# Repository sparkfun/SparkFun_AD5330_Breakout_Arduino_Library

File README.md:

AD5330 Breakout Arduino Library
===============

[ 
*Breakout Board for AD5330 Parallel 8-Bit DAC (BOB-12082)*](https://www.sparkfun.com/products/12082)

This is a breakout board for Analog Device's AD5330 8-bit digital-to-analog converter. 
It runs from 2.5 to 5.5V. 

Repository Contents
-------------------

* **/examples** - Example sketches for the library (.ino). Run these from the Arduino IDE. 
* **/extras** - Additional documentation for the user. These files are ignored by the IDE. 
* **/src** - Source files for the library (.cpp, .h).
* **keywords.txt** - Keywords from this library that will be highlighted in the Arduino IDE. 
* **library.properties** - General library properties for the Arduino package manager. 

Documentation
--------------

* **[Installing an Arduino Library Guide](https://learn.sparkfun.com/tutorials/installing-an-arduino-library)** - Basic information on how to install an Arduino library.
* **[Product Repository](https://github.com/sparkfun/AD5330_Breakout)** - Main repository (including hardware files) for the AD5330 Breakout.
* **[Tutorial](http://www.sparkfun.com/commerce/tutorial_info.php?tutorials_id=160)** - Basic tutorial for the AD5330 Breakout.

Version History
---------------

* [V_1.2.2](https://github.com/sparkfun/AD5330_Breakout_Arduino_Library/tree/V_1.2.2) - Edited README.txt
* [V_1.2.1](https://github.com/sparkfun/AD5330_Breakout_Arduino_Library/tree/V_1.2.1) - Fixed library.properties file
* [V1.2](https://github.com/sparkfun/AD5330_Breakout_Arduino_Library/tree/V_1.2) - Arduino library format
* [V1.1](https://www.sparkfun.com/products/9719) 

License Information
-------------------
The hardware is released under [Creative Commons Share-alike 3.0](http://creativecommons.org/licenses/by-sa/3.0/).  
All other code is open source so please feel free to do anything you want with it; you buy me a beer if you use this and we meet someday ([Beerware license](http://en.wikipedia.org/wiki/Beerware)).

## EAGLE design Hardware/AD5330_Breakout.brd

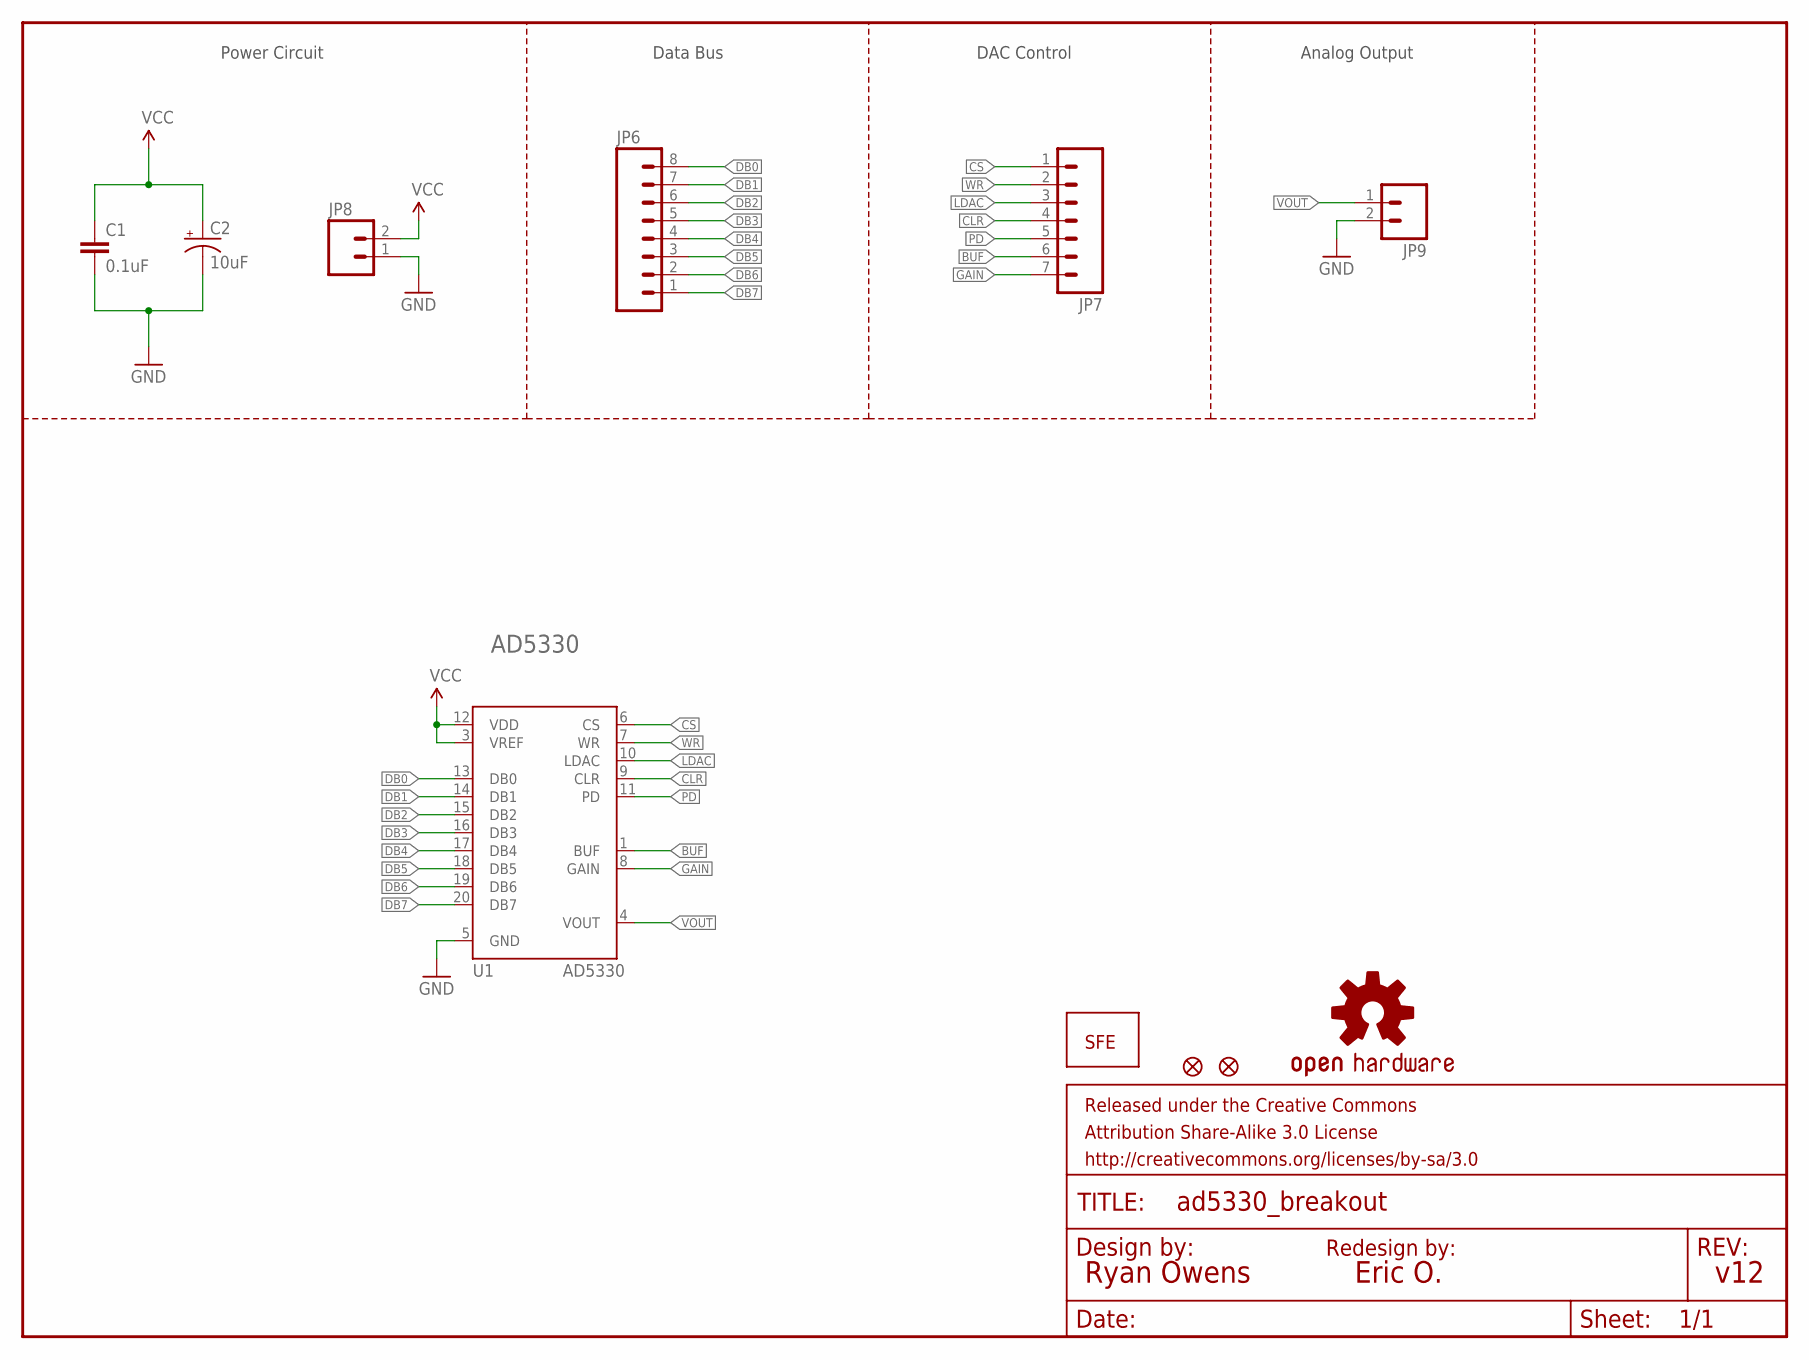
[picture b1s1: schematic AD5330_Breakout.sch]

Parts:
C1: 0.1uF; 0603-CAP
C2: 10uF; EIA3216
FRAME1: FRAME-LETTER; CREATIVE_COMMONS
JP1: LOGO-SFENEW; SFE-NEW-WEBLOGO
JP2, JP3: FIDUCIAL1X2; FIDUCIAL-1X2
JP6: M08; 1X08
JP7: M07; 1X07
JP8, JP9: M02PTH; 1X02
LOGO1: OSHW-LOGOS; OSHW-LOGO-S
U1: AD5330; TSSOP20

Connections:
BUF: JP7.6, U1.1 (BUF)
CLR: JP7.4, U1.9 (CLR)
CS: JP7.1, U1.6 (CS)
DB0: JP6.8, U1.13 (DB0)
DB1: JP6.7, U1.14 (DB1)
DB2: JP6.6, U1.15 (DB2)
DB3: JP6.5, U1.16 (DB3)
DB4: JP6.4, U1.17 (DB4)
DB5: JP6.3, U1.18 (DB5)
DB6: JP6.2, U1.19 (DB6)
DB7: JP6.1, U1.20 (DB7)
GAIN: JP7.7, U1.8 (GAIN)
GND: C1.2, C2.C (-), JP8.1, JP9.2, U1.5 (GND)
LDAC: JP7.3, U1.10 (LDAC)
PD: JP7.5, U1.11 (PD)
VCC: C1.1, C2.A (+), JP8.2, U1.3 (VREF), U1.12 (VDD)
VOUT: JP9.1, U1.4 (VOUT)
WR: JP7.2, U1.7 (WR)

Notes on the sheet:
Power Circuit
Data Bus
DAC Control
Analog Output
v12
Ryan Owens
Redesign by:
Eric O.
AD5330

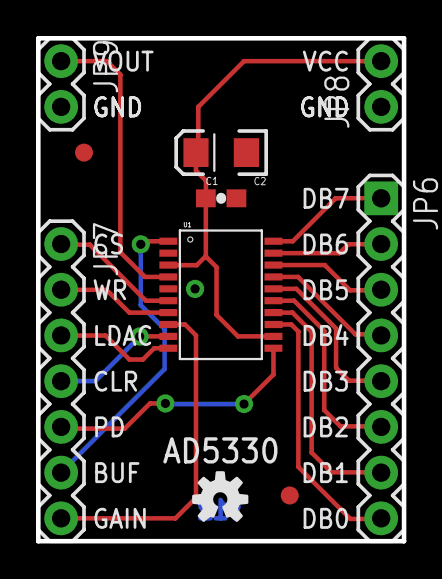
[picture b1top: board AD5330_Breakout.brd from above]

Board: 2 copper layers, 20.3 x 27.9 mm, 12 parts (1 on the bottom side), 18 nets.

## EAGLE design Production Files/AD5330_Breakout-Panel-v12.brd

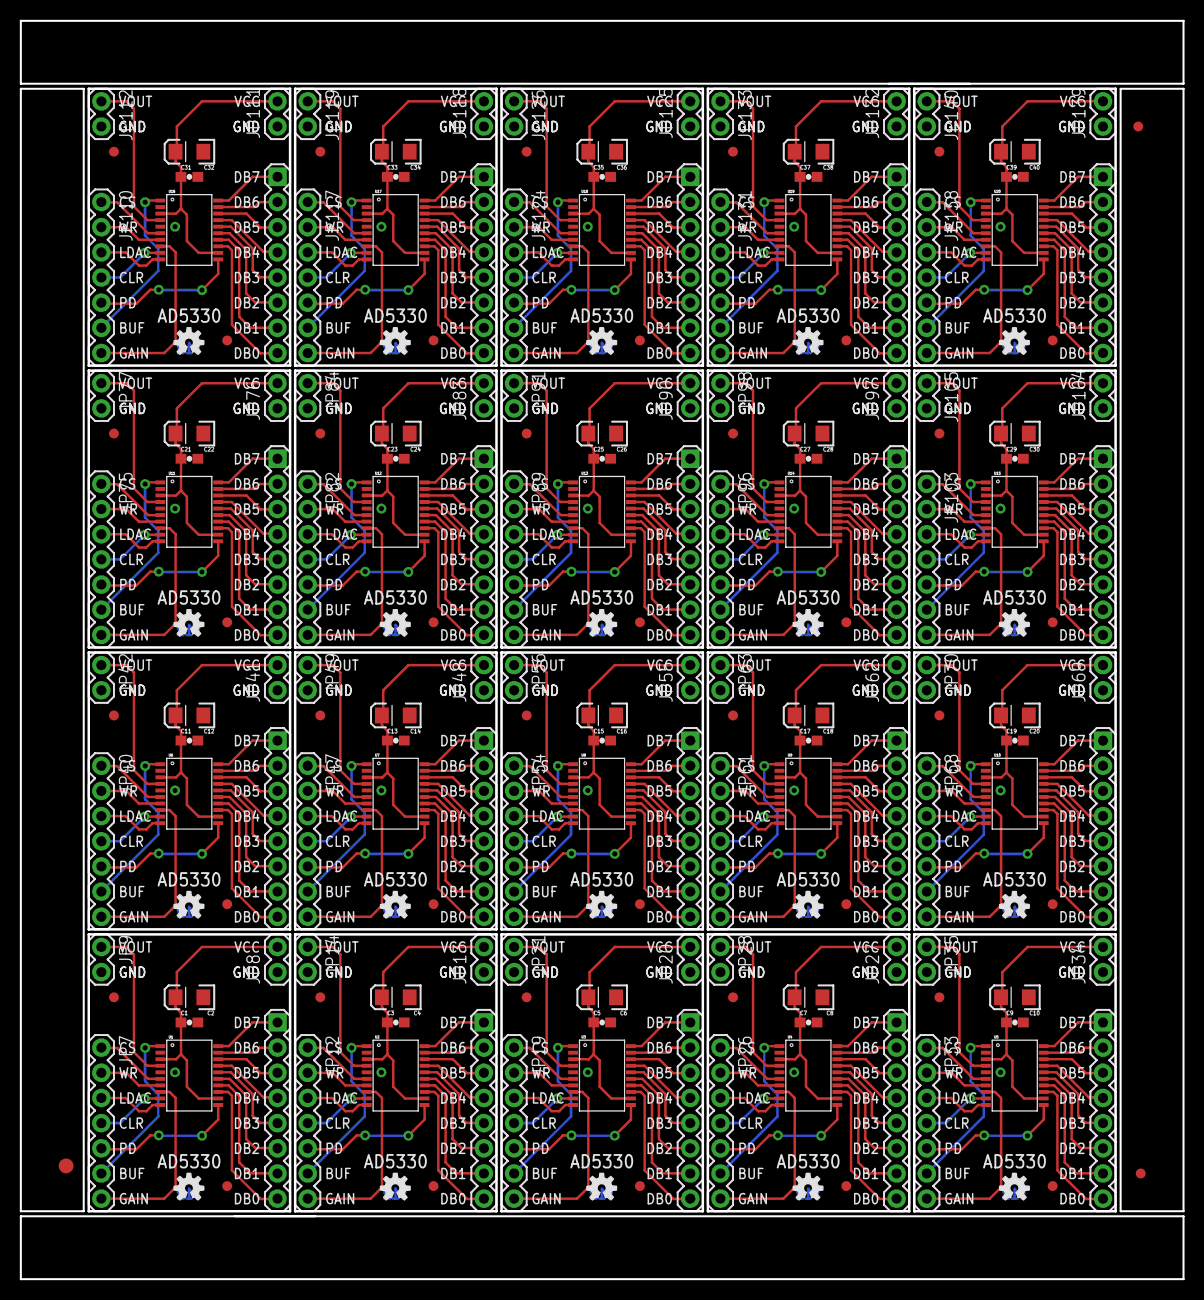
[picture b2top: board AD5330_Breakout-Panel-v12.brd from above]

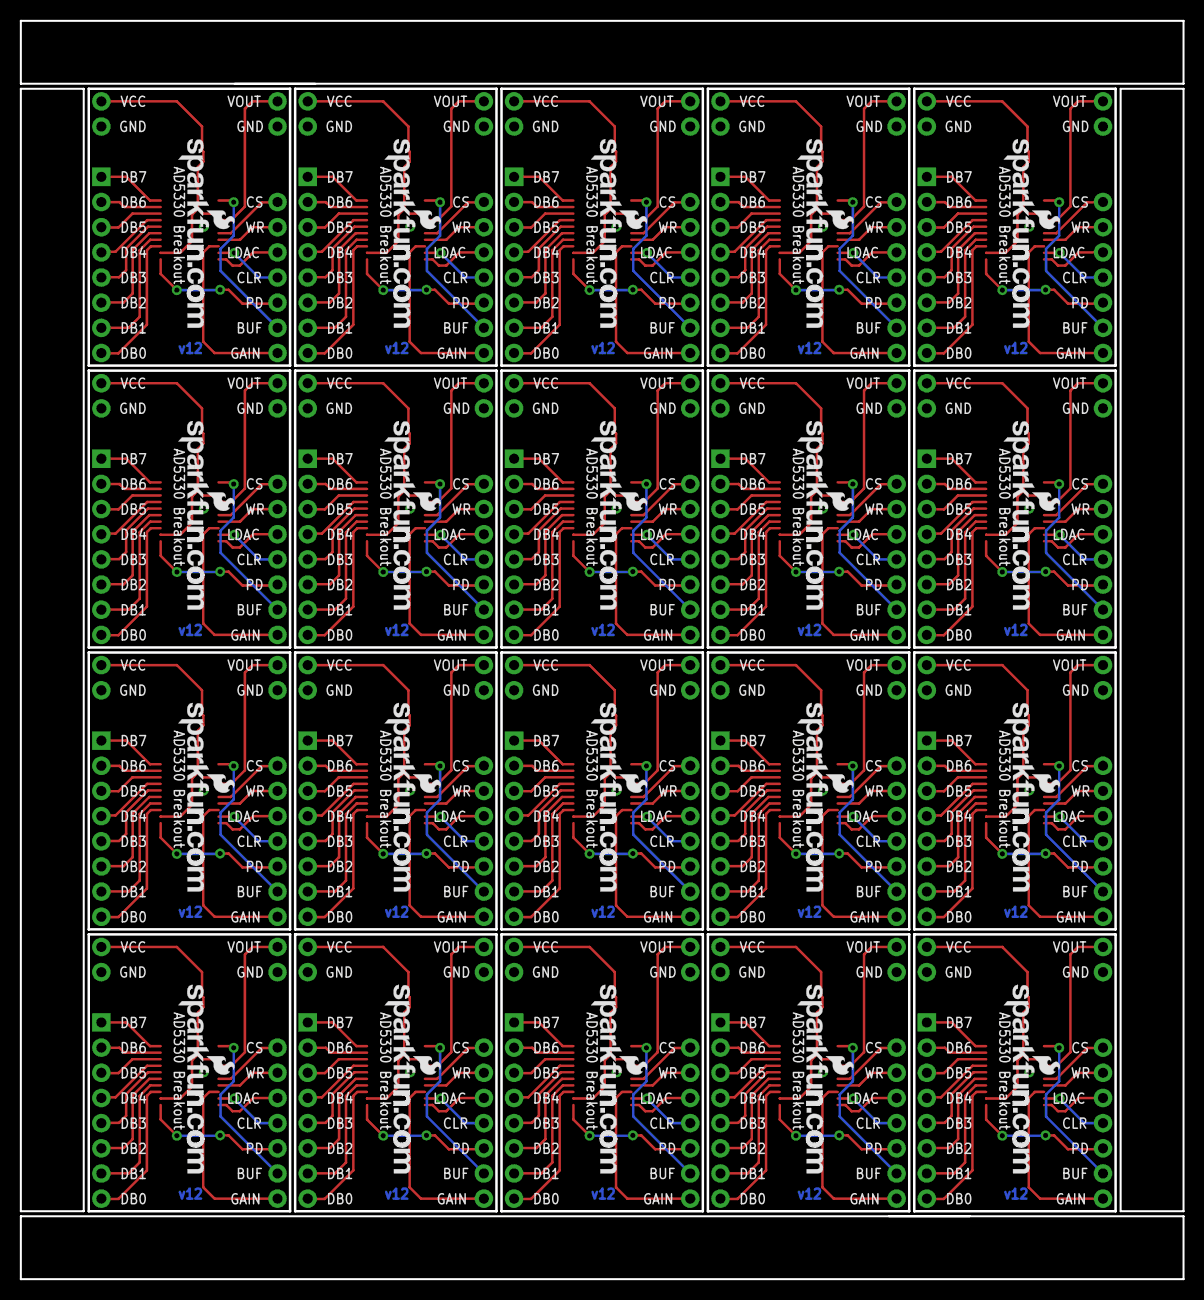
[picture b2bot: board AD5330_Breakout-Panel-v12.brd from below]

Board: 2 copper layers, 117.3 x 126.9 mm, 223 parts (20 on the bottom side), 360 nets.

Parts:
C1, C3, C5, C7, C9, C11, C13, C15, C17, C19, C21, C23, C25, C27, C29, C31, C33, C35, C37, C39: 0.1uF; 0603-CAP
C2, C4, C6, C8, C10, C12, C14, C16, C18, C20, C22, C24, C26, C28, C30, C32, C34, C36, C38, C40: 10uF; EIA3216
E$1: FIDUCIAL-1.5X3
E$4, E$5: FIDUCIAL-1X2
JP1, JP4, JP15, JP22, JP29, JP36, JP43, JP50, JP57, JP64, JP71, JP78, JP85, JP92, JP99, JP106, JP113, JP120, JP127, JP134: LOGO-SFENEW; SFE-NEW-WEBLOGO
JP2, JP3, JP5, JP10, JP16, JP17, JP23, JP24, JP30, JP31, JP37, JP38, JP44, JP45, JP51, JP52, JP58, JP59, JP65, JP66, JP72, JP73, JP79, JP80, JP86, JP87, JP93, JP94, JP100, JP101, JP107, JP108, JP114, JP115, JP121, JP122, JP128, JP129, JP135, JP136: FIDUCIAL1X2; FIDUCIAL-1X2
JP6, JP11, JP18, JP25, JP32, JP39, JP46, JP53, JP60, JP67, JP74, JP81, JP88, JP95, JP102, JP109, JP116, JP123, JP130, JP137: 1X08
JP7, JP12, JP19, JP26, JP33, JP40, JP47, JP54, JP61, JP68, JP75, JP82, JP89, JP96, JP103, JP110, JP117, JP124, JP131, JP138: 1X07
JP8, JP9, JP13, JP14, JP20, JP21, JP27, JP28, JP34, JP35, JP41, JP42, JP48, JP49, JP55, JP56, JP62, JP63, JP69, JP70, JP76, JP77, JP83, JP84, JP90, JP91, JP97, JP98, JP104, JP105, JP111, JP112, JP118, JP119, JP125, JP126, JP132, JP133, JP139, JP140: 1X02
LOGO1, LOGO2, LOGO3, LOGO4, LOGO5, LOGO6, LOGO7, LOGO8, LOGO9, LOGO10, LOGO11, LOGO12, LOGO13, LOGO14, LOGO15, LOGO16, LOGO17, LOGO18, LOGO19, LOGO20: OSHW-LOGOS; OSHW-LOGO-S
U1, U2, U3, U4, U5, U6, U7, U8, U9, U10, U11, U12, U13, U14, U15, U16, U17, U18, U19, U20: AD5330; TSSOP20

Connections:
BUF: JP7.6, U1.1
BUF1: JP12.6, U2.1
BUF2: JP19.6, U3.1
BUF3: JP26.6, U4.1
BUF4: JP33.6, U5.1
BUF5: JP40.6, U6.1
BUF6: JP47.6, U7.1
BUF7: JP54.6, U8.1
BUF8: JP61.6, U9.1
BUF9: JP68.6, U10.1
BUF10: JP75.6, U11.1
BUF11: JP82.6, U12.1
BUF12: JP89.6, U13.1
BUF13: JP96.6, U14.1
BUF14: JP103.6, U15.1
BUF15: JP110.6, U16.1
BUF16: JP117.6, U17.1
BUF17: JP124.6, U18.1
BUF18: JP131.6, U19.1
BUF19: JP138.6, U20.1
CLR: JP7.4, U1.9
CLR1: JP12.4, U2.9
CLR2: JP19.4, U3.9
CLR3: JP26.4, U4.9
CLR4: JP33.4, U5.9
CLR5: JP40.4, U6.9
CLR6: JP47.4, U7.9
CLR7: JP54.4, U8.9
CLR8: JP61.4, U9.9
CLR9: JP68.4, U10.9
CLR10: JP75.4, U11.9
CLR11: JP82.4, U12.9
CLR12: JP89.4, U13.9
CLR13: JP96.4, U14.9
CLR14: JP103.4, U15.9
CLR15: JP110.4, U16.9
CLR16: JP117.4, U17.9
CLR17: JP124.4, U18.9
CLR18: JP131.4, U19.9
CLR19: JP138.4, U20.9
CS: JP7.1, U1.6
CS1: JP12.1, U2.6
CS2: JP19.1, U3.6
CS3: JP26.1, U4.6
CS4: JP33.1, U5.6
CS5: JP40.1, U6.6
CS6: JP47.1, U7.6
CS7: JP54.1, U8.6
CS8: JP61.1, U9.6
CS9: JP68.1, U10.6
CS10: JP75.1, U11.6
CS11: JP82.1, U12.6
CS12: JP89.1, U13.6
CS13: JP96.1, U14.6
CS14: JP103.1, U15.6
CS15: JP110.1, U16.6
CS16: JP117.1, U17.6
CS17: JP124.1, U18.6
CS18: JP131.1, U19.6
CS19: JP138.1, U20.6
DB0: JP6.8, U1.13
DB1: JP6.7, U1.14
DB2: JP6.6, U1.15
DB3: JP6.5, U1.16
DB4: JP6.4, U1.17
DB5: JP6.3, U1.18
DB6: JP6.2, U1.19
DB7: JP6.1, U1.20
DB8: JP11.8, U2.13
DB9: JP11.7, U2.14
DB10: JP11.6, U2.15
DB11: JP11.5, U2.16
DB12: JP11.4, U2.17
DB13: JP11.3, U2.18
DB14: JP11.2, U2.19
DB15: JP11.1, U2.20
DB16: JP18.8, U3.13
DB17: JP18.7, U3.14
DB18: JP18.6, U3.15
DB19: JP18.5, U3.16
DB20: JP18.4, U3.17
DB21: JP18.3, U3.18
DB22: JP18.2, U3.19
DB23: JP18.1, U3.20
DB24: JP25.8, U4.13
DB25: JP25.7, U4.14
DB26: JP25.6, U4.15
DB27: JP25.5, U4.16
DB28: JP25.4, U4.17
DB29: JP25.3, U4.18
DB30: JP25.2, U4.19
DB31: JP25.1, U4.20
DB32: JP32.8, U5.13
DB33: JP32.7, U5.14
DB34: JP32.6, U5.15
DB35: JP32.5, U5.16
DB36: JP32.4, U5.17
DB37: JP32.3, U5.18
DB38: JP32.2, U5.19
DB39: JP32.1, U5.20
DB40: JP39.8, U6.13
DB41: JP39.7, U6.14
DB42: JP39.6, U6.15
DB43: JP39.5, U6.16
DB44: JP39.4, U6.17
DB45: JP39.3, U6.18
DB46: JP39.2, U6.19
DB47: JP39.1, U6.20
DB48: JP46.8, U7.13
DB49: JP46.7, U7.14
DB50: JP46.6, U7.15
DB51: JP46.5, U7.16
DB52: JP46.4, U7.17
DB53: JP46.3, U7.18
DB54: JP46.2, U7.19
DB55: JP46.1, U7.20
DB56: JP53.8, U8.13
DB57: JP53.7, U8.14
DB58: JP53.6, U8.15
DB59: JP53.5, U8.16
DB60: JP53.4, U8.17
DB61: JP53.3, U8.18
DB62: JP53.2, U8.19
DB63: JP53.1, U8.20
DB64: JP60.8, U9.13
DB65: JP60.7, U9.14
DB66: JP60.6, U9.15
DB67: JP60.5, U9.16
DB68: JP60.4, U9.17
DB69: JP60.3, U9.18
DB70: JP60.2, U9.19
DB71: JP60.1, U9.20
DB72: JP67.8, U10.13
DB73: JP67.7, U10.14
DB74: JP67.6, U10.15
DB75: JP67.5, U10.16
DB76: JP67.4, U10.17
DB77: JP67.3, U10.18
DB78: JP67.2, U10.19
DB79: JP67.1, U10.20
DB80: JP74.8, U11.13
DB81: JP74.7, U11.14
DB82: JP74.6, U11.15
DB83: JP74.5, U11.16
DB84: JP74.4, U11.17
DB85: JP74.3, U11.18
DB86: JP74.2, U11.19
DB87: JP74.1, U11.20
DB88: JP81.8, U12.13
DB89: JP81.7, U12.14
DB90: JP81.6, U12.15
DB91: JP81.5, U12.16
DB92: JP81.4, U12.17
DB93: JP81.3, U12.18
DB94: JP81.2, U12.19
DB95: JP81.1, U12.20
DB96: JP88.8, U13.13
DB97: JP88.7, U13.14
DB98: JP88.6, U13.15
DB99: JP88.5, U13.16
DB100: JP88.4, U13.17
DB101: JP88.3, U13.18
DB102: JP88.2, U13.19
DB103: JP88.1, U13.20
DB104: JP95.8, U14.13
DB105: JP95.7, U14.14
DB106: JP95.6, U14.15
DB107: JP95.5, U14.16
DB108: JP95.4, U14.17
DB109: JP95.3, U14.18
DB110: JP95.2, U14.19
DB111: JP95.1, U14.20
DB112: JP102.8, U15.13
DB113: JP102.7, U15.14
DB114: JP102.6, U15.15
DB115: JP102.5, U15.16
DB116: JP102.4, U15.17
DB117: JP102.3, U15.18
DB118: JP102.2, U15.19
DB119: JP102.1, U15.20
DB120: JP109.8, U16.13
DB121: JP109.7, U16.14
DB122: JP109.6, U16.15
DB123: JP109.5, U16.16
DB124: JP109.4, U16.17
DB125: JP109.3, U16.18
DB126: JP109.2, U16.19
DB127: JP109.1, U16.20
DB128: JP116.8, U17.13
DB129: JP116.7, U17.14
DB130: JP116.6, U17.15
DB131: JP116.5, U17.16
DB132: JP116.4, U17.17
DB133: JP116.3, U17.18
DB134: JP116.2, U17.19
DB135: JP116.1, U17.20
DB136: JP123.8, U18.13
DB137: JP123.7, U18.14
DB138: JP123.6, U18.15
DB139: JP123.5, U18.16
DB140: JP123.4, U18.17
DB141: JP123.3, U18.18
DB142: JP123.2, U18.19
DB143: JP123.1, U18.20
DB144: JP130.8, U19.13
DB145: JP130.7, U19.14
DB146: JP130.6, U19.15
DB147: JP130.5, U19.16
DB148: JP130.4, U19.17
DB149: JP130.3, U19.18
DB150: JP130.2, U19.19
DB151: JP130.1, U19.20
DB152: JP137.8, U20.13
DB153: JP137.7, U20.14
DB154: JP137.6, U20.15
DB155: JP137.5, U20.16
DB156: JP137.4, U20.17
DB157: JP137.3, U20.18
DB158: JP137.2, U20.19
DB159: JP137.1, U20.20
GAIN: JP7.7, U1.8
GAIN1: JP12.7, U2.8
GAIN2: JP19.7, U3.8
GAIN3: JP26.7, U4.8
GAIN4: JP33.7, U5.8
GAIN5: JP40.7, U6.8
GAIN6: JP47.7, U7.8
GAIN7: JP54.7, U8.8
GAIN8: JP61.7, U9.8
GAIN9: JP68.7, U10.8
GAIN10: JP75.7, U11.8
GAIN11: JP82.7, U12.8
GAIN12: JP89.7, U13.8
GAIN13: JP96.7, U14.8
GAIN14: JP103.7, U15.8
GAIN15: JP110.7, U16.8
GAIN16: JP117.7, U17.8
GAIN17: JP124.7, U18.8
GAIN18: JP131.7, U19.8
GAIN19: JP138.7, U20.8
GND: C1.2, C2.C, JP8.1, JP9.2, U1.5
GND1: C3.2, C4.C, JP13.1, JP14.2, U2.5
GND2: C5.2, C6.C, JP20.1, JP21.2, U3.5
GND3: C7.2, C8.C, JP27.1, JP28.2, U4.5
GND4: C9.2, C10.C, JP34.1, JP35.2, U5.5
GND5: C11.2, C12.C, JP41.1, JP42.2, U6.5
GND6: C13.2, C14.C, JP48.1, JP49.2, U7.5
GND7: C15.2, C16.C, JP55.1, JP56.2, U8.5
GND8: C17.2, C18.C, JP62.1, JP63.2, U9.5
GND9: C19.2, C20.C, JP69.1, JP70.2, U10.5
GND10: C21.2, C22.C, JP76.1, JP77.2, U11.5
GND11: C23.2, C24.C, JP83.1, JP84.2, U12.5
GND12: C25.2, C26.C, JP90.1, JP91.2, U13.5
GND13: C27.2, C28.C, JP97.1, JP98.2, U14.5
GND14: C29.2, C30.C, JP104.1, JP105.2, U15.5
GND15: C31.2, C32.C, JP111.1, JP112.2, U16.5
GND16: C33.2, C34.C, JP118.1, JP119.2, U17.5
GND17: C35.2, C36.C, JP125.1, JP126.2, U18.5
GND18: C37.2, C38.C, JP132.1, JP133.2, U19.5
GND19: C39.2, C40.C, JP139.1, JP140.2, U20.5
LDAC: JP7.3, U1.10
LDAC1: JP12.3, U2.10
LDAC2: JP19.3, U3.10
LDAC3: JP26.3, U4.10
LDAC4: JP33.3, U5.10
LDAC5: JP40.3, U6.10
LDAC6: JP47.3, U7.10
LDAC7: JP54.3, U8.10
LDAC8: JP61.3, U9.10
LDAC9: JP68.3, U10.10
LDAC10: JP75.3, U11.10
LDAC11: JP82.3, U12.10
LDAC12: JP89.3, U13.10
LDAC13: JP96.3, U14.10
LDAC14: JP103.3, U15.10
LDAC15: JP110.3, U16.10
LDAC16: JP117.3, U17.10
LDAC17: JP124.3, U18.10
LDAC18: JP131.3, U19.10
LDAC19: JP138.3, U20.10
PD: JP7.5, U1.11
PD1: JP12.5, U2.11
PD2: JP19.5, U3.11
PD3: JP26.5, U4.11
PD4: JP33.5, U5.11
PD5: JP40.5, U6.11
PD6: JP47.5, U7.11
PD7: JP54.5, U8.11
PD8: JP61.5, U9.11
PD9: JP68.5, U10.11
PD10: JP75.5, U11.11
PD11: JP82.5, U12.11
PD12: JP89.5, U13.11
PD13: JP96.5, U14.11
PD14: JP103.5, U15.11
PD15: JP110.5, U16.11
PD16: JP117.5, U17.11
PD17: JP124.5, U18.11
PD18: JP131.5, U19.11
PD19: JP138.5, U20.11
VCC: C1.1, C2.A, JP8.2, U1.3, U1.12
VCC1: C3.1, C4.A, JP13.2, U2.3, U2.12
VCC2: C5.1, C6.A, JP20.2, U3.3, U3.12
VCC3: C7.1, C8.A, JP27.2, U4.3, U4.12
VCC4: C9.1, C10.A, JP34.2, U5.3, U5.12
VCC5: C11.1, C12.A, JP41.2, U6.3, U6.12
VCC6: C13.1, C14.A, JP48.2, U7.3, U7.12
VCC7: C15.1, C16.A, JP55.2, U8.3, U8.12
VCC8: C17.1, C18.A, JP62.2, U9.3, U9.12
VCC9: C19.1, C20.A, JP69.2, U10.3, U10.12
VCC10: C21.1, C22.A, JP76.2, U11.3, U11.12
VCC11: C23.1, C24.A, JP83.2, U12.3, U12.12
VCC12: C25.1, C26.A, JP90.2, U13.3, U13.12
VCC13: C27.1, C28.A, JP97.2, U14.3, U14.12
VCC14: C29.1, C30.A, JP104.2, U15.3, U15.12
VCC15: C31.1, C32.A, JP111.2, U16.3, U16.12
VCC16: C33.1, C34.A, JP118.2, U17.3, U17.12
VCC17: C35.1, C36.A, JP125.2, U18.3, U18.12
VCC18: C37.1, C38.A, JP132.2, U19.3, U19.12
VCC19: C39.1, C40.A, JP139.2, U20.3, U20.12
VOUT: JP9.1, U1.4
VOUT1: JP14.1, U2.4
VOUT2: JP21.1, U3.4
VOUT3: JP28.1, U4.4
VOUT4: JP35.1, U5.4
VOUT5: JP42.1, U6.4
VOUT6: JP49.1, U7.4
VOUT7: JP56.1, U8.4
VOUT8: JP63.1, U9.4
VOUT9: JP70.1, U10.4
VOUT10: JP77.1, U11.4
VOUT11: JP84.1, U12.4
VOUT12: JP91.1, U13.4
VOUT13: JP98.1, U14.4
VOUT14: JP105.1, U15.4
VOUT15: JP112.1, U16.4
VOUT16: JP119.1, U17.4
VOUT17: JP126.1, U18.4
VOUT18: JP133.1, U19.4
VOUT19: JP140.1, U20.4
WR: JP7.2, U1.7
WR1: JP12.2, U2.7
WR2: JP19.2, U3.7
WR3: JP26.2, U4.7
WR4: JP33.2, U5.7
WR5: JP40.2, U6.7
WR6: JP47.2, U7.7
WR7: JP54.2, U8.7
WR8: JP61.2, U9.7
WR9: JP68.2, U10.7
WR10: JP75.2, U11.7
WR11: JP82.2, U12.7
WR12: JP89.2, U13.7
WR13: JP96.2, U14.7
WR14: JP103.2, U15.7
WR15: JP110.2, U16.7
WR16: JP117.2, U17.7
WR17: JP124.2, U18.7
WR18: JP131.2, U19.7
WR19: JP138.2, U20.7

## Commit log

2013-09-26 Initial Commit
    -gitignore
    -v11 .brd and .sch
2013-09-26 Revision changes
    -Cleaned up schematic
    -Added OSHW Logo
    -0402->0603
    -Added 10uf cap for filtration off of VDD as per the datasheet
2013-09-27 Added pin silk on bottom
2013-10-04 Cleaned up schematic further
    Grouped circuits together
2013-10-21 Panel Created
2014-01-06 Adding Arduino Library and updating README
2015-04-24 Updating to new library structure
2015-04-24 fixed readme typo
2015-04-29 Fixed library.properties and version increment
2015-04-29 Edited README.txt
2015-05-13 Updating attributes, library properties
2015-05-13 Fixing lib.properties github url
2025-06-27 Update README.md
    Updating link

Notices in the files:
parts and their libraries:
SparkFun-Aesthetics: Licensing: CC v3.0 Share-Alike You are welcome to use this library for commercial purposes.
SparkFun-Aesthetics: Released under the Creative Commons Attribution Share-Alike 3.0 License
SparkFun-Aesthetics: Released under the Creative Commons
